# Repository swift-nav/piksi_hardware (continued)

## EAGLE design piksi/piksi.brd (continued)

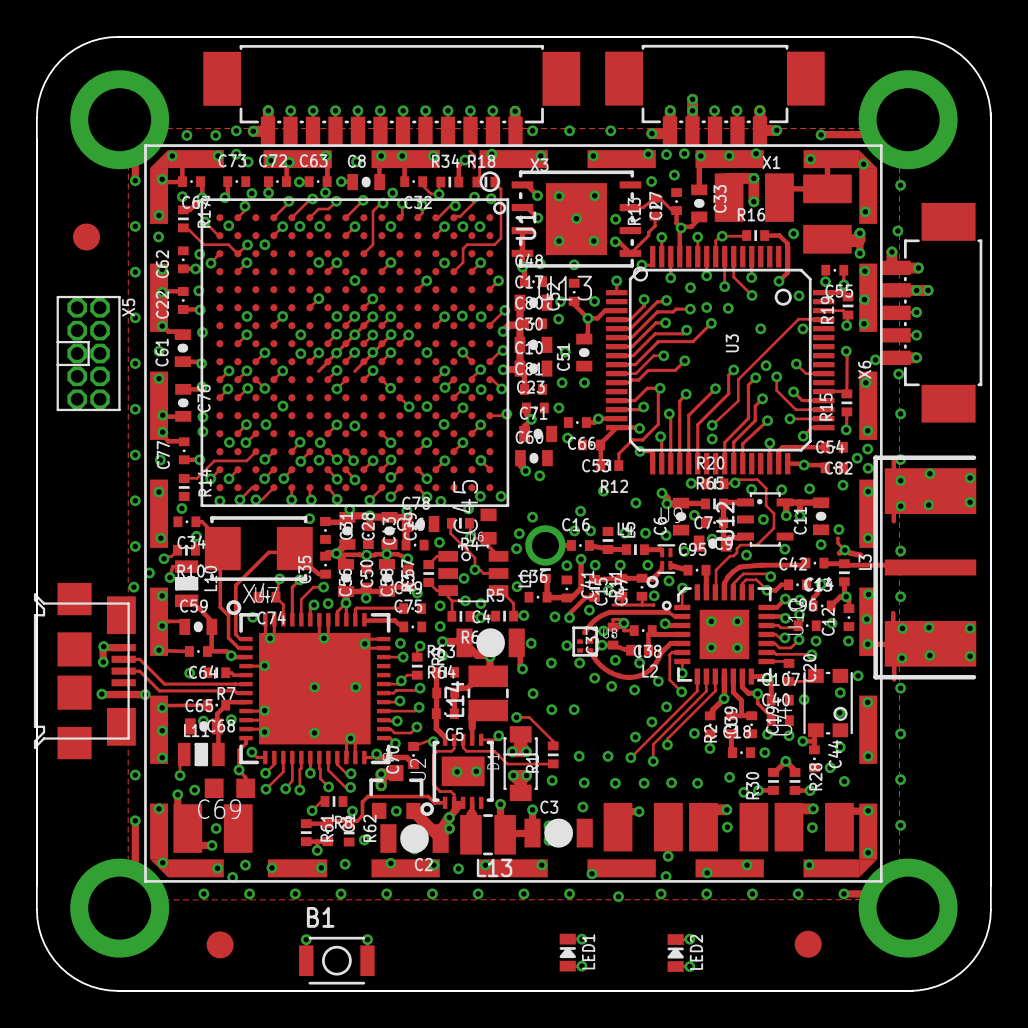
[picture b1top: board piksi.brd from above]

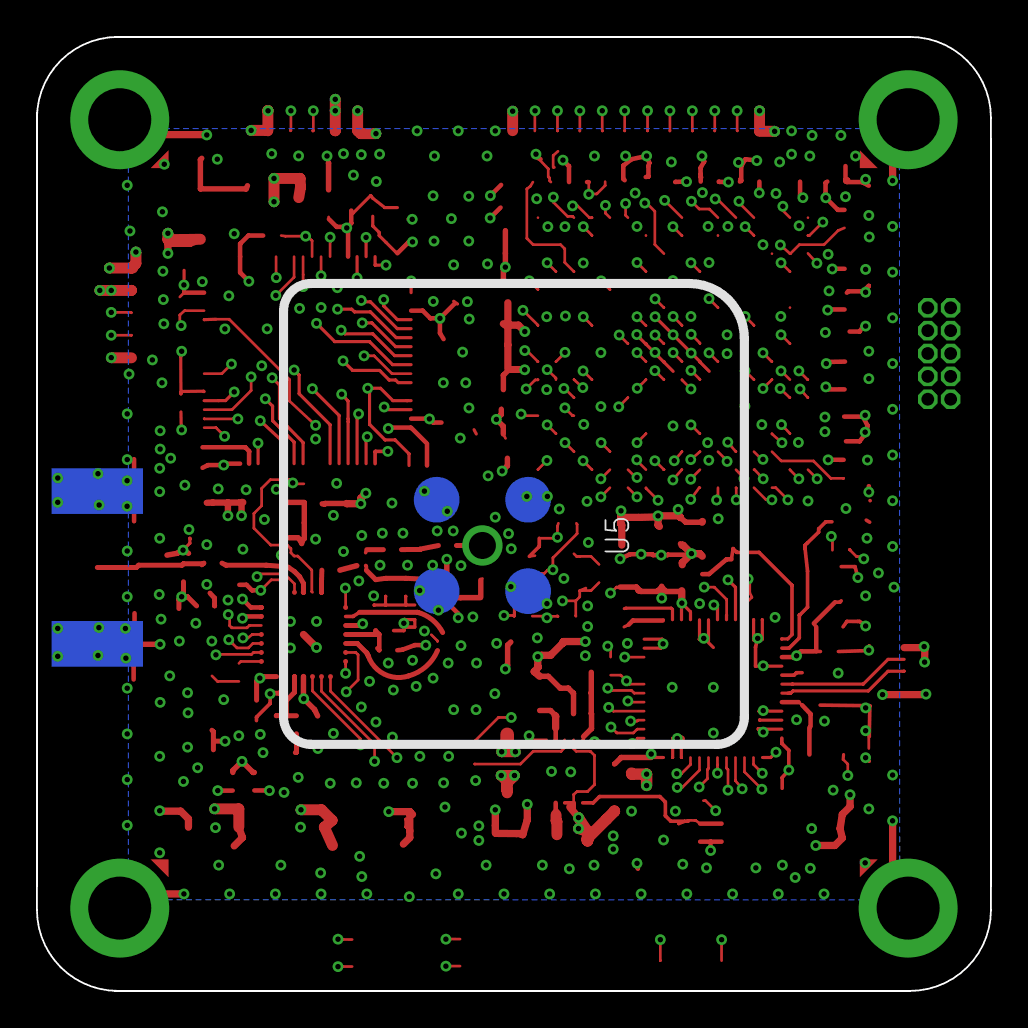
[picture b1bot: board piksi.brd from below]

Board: 6 copper layers, 53.0 x 53.0 mm, 157 parts (2 on the bottom side), 115 nets.

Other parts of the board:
U$1: LOGOINITIALS; INITIALS

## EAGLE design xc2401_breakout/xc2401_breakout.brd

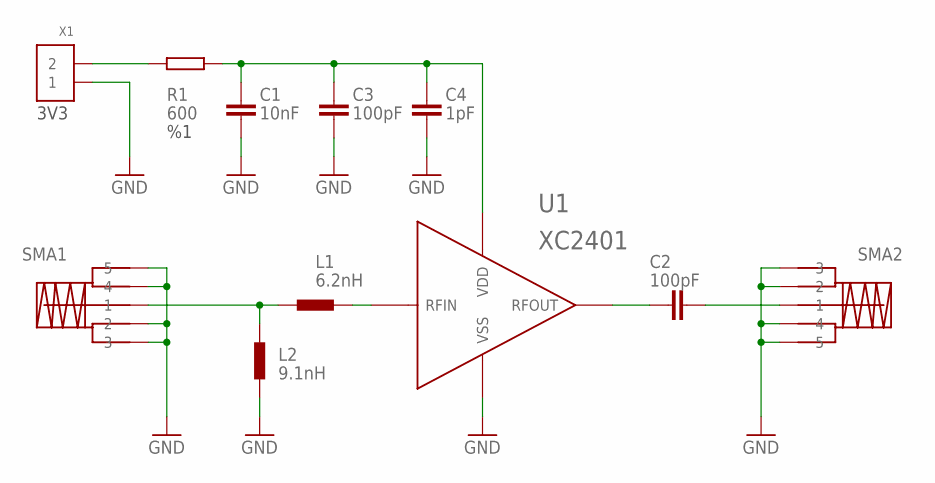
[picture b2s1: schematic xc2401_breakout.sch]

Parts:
C1: 10nF; 0402-CAP
C2, C3: 100pF; 0402-CAP
C4: 1pF; 0402-CAP
L1: 6.2nH; 0402-IND
L2: 9.1nH; 0402-IND
R1: 600; 0402-RES
SMA1, SMA2: SMA_EDGE
U1: XC2401
X1: CONN_2-1-53261; PB-53261-02

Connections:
GND: C1.P$2 (2), C3.P$2 (2), C4.P$2 (2), L2.P$1 (1), SMA1.P2 (2), SMA1.P3 (3), SMA1.P4 (4), SMA1.P5 (5), SMA2.P2 (2), SMA2.P3 (3), SMA2.P4 (4), SMA2.P5 (5), U1.3 (VSS), X1.1
unnamed: C1.P$1 (1), C3.P$1 (1), C4.P$1 (1), R1.P$2 (2), U1.1 (VDD)
unnamed: C2.P$1 (1), U1.2 (RFOUT)
unnamed: C2.P$2 (2), SMA2.P1 (1)
unnamed: L1.P$1 (1), L2.P$2 (2), SMA1.P1 (1)
unnamed: L1.P$2 (2), U1.4 (RFIN)
unnamed: R1.P$1 (1), X1.2

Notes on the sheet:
3V3

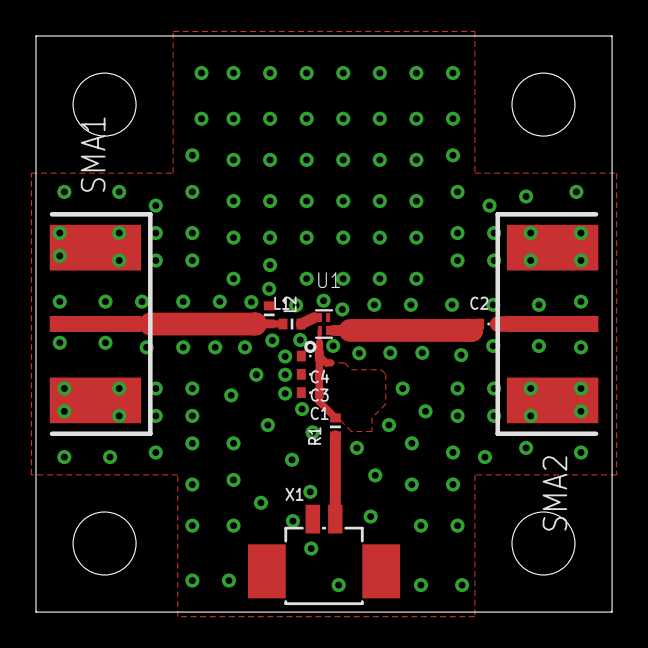
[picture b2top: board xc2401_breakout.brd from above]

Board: 2 copper layers, 32.0 x 32.0 mm, 11 parts (0 on the bottom side), 7 nets.

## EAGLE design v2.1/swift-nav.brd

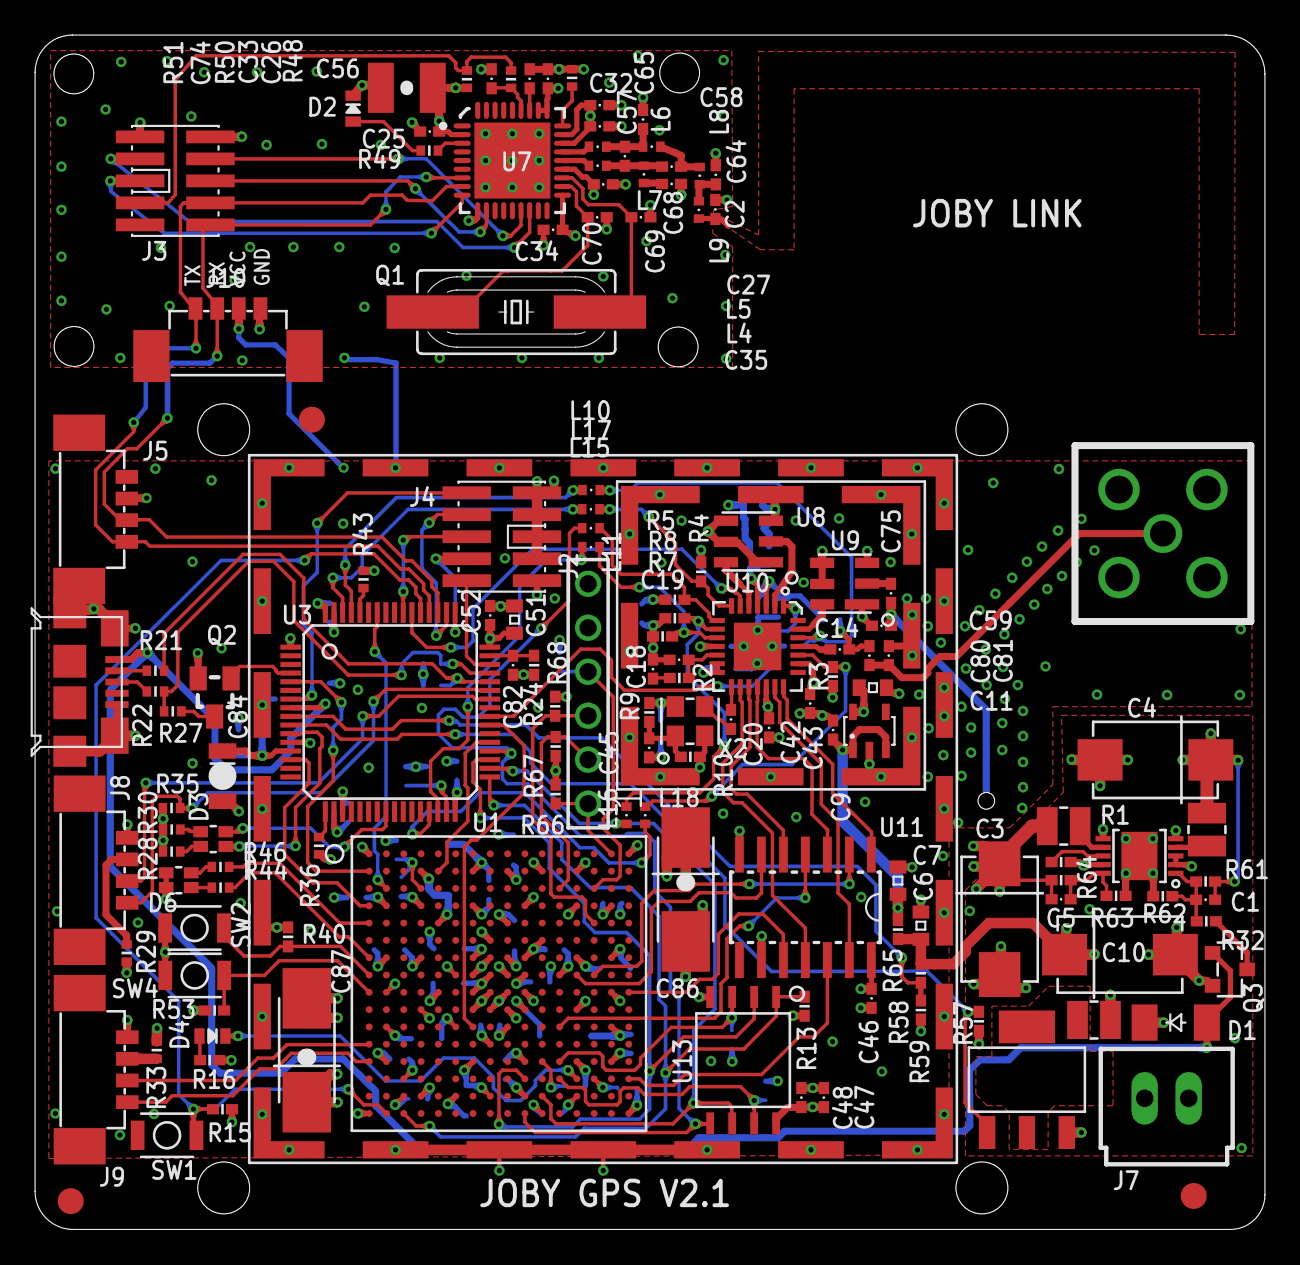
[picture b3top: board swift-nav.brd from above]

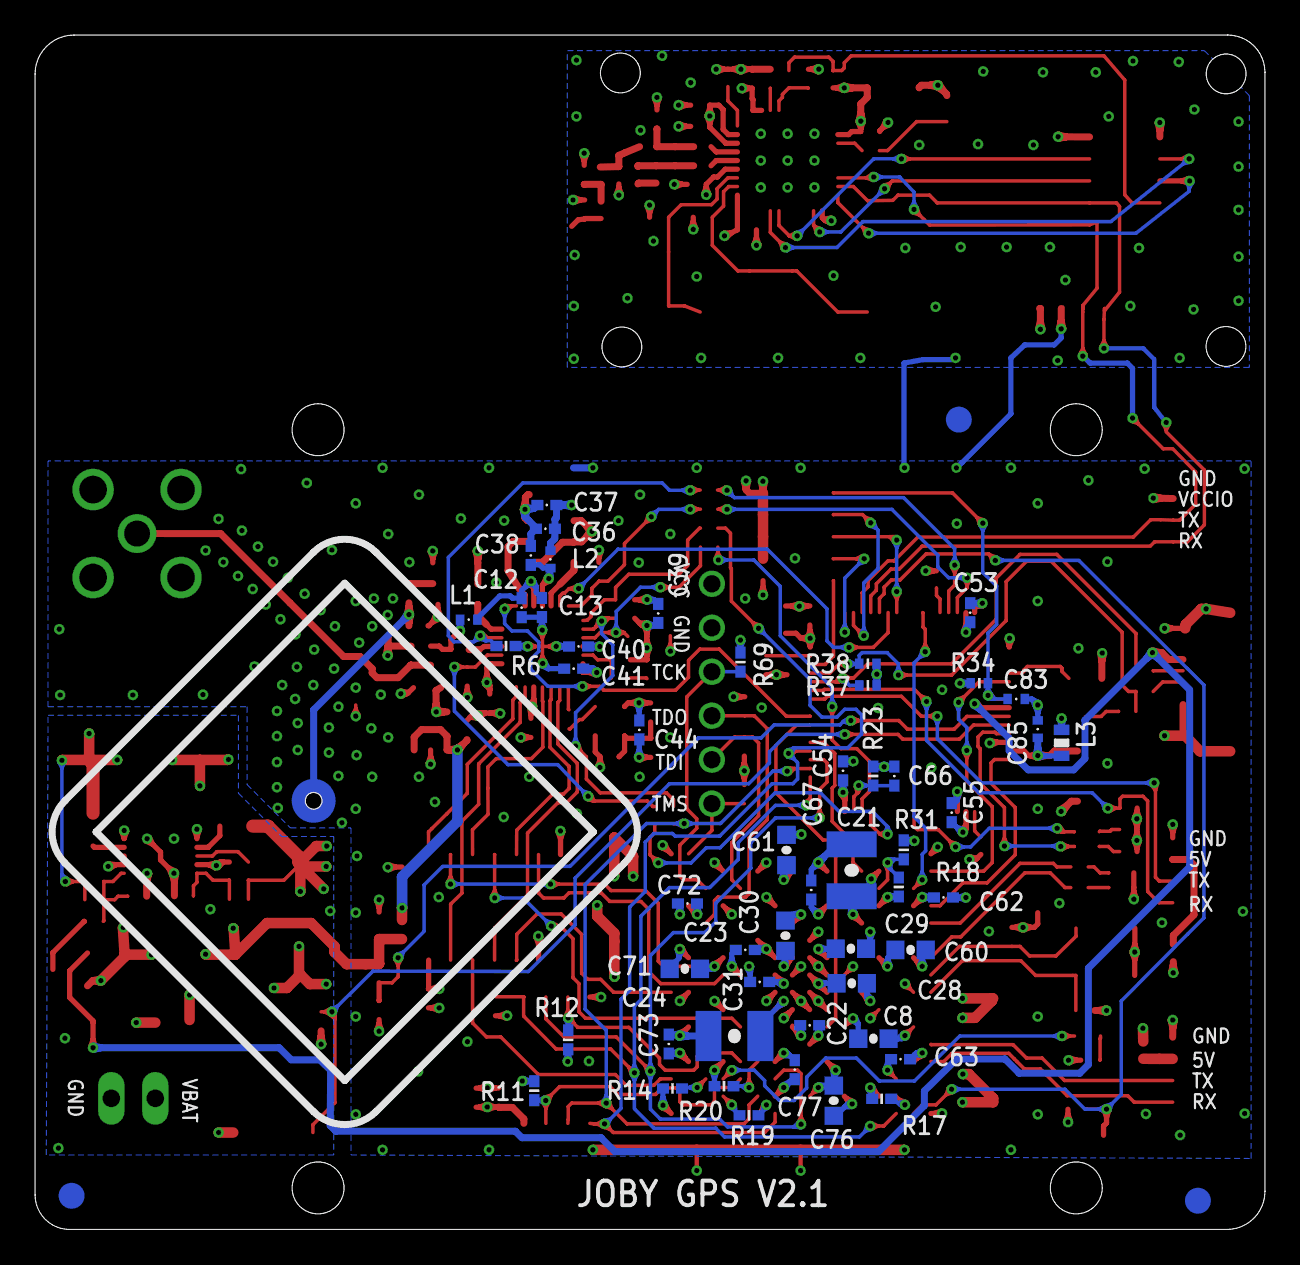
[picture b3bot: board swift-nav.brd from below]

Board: 4 copper layers, 71.0 x 69.0 mm, 198 parts (55 on the bottom side), 131 nets.

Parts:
ANT1: GPS_PATCH_ANTENNA
C1, C5: 22pF; C0402
C2, C59, C64, C81: DNP; C0402
C3, C4, C10: 10UF_TANT; CT7343
C6, C7: 2.2uF; 0603
C8, C28, C29, C30, C60, C61, C71, C76: 4.7uF; C0603K
C9, C44, C45, C48: 0.01uF; C0402
C11: 10uF; 0603
C12, C14, C37, C68: 100pF; C0402
C13, C20, C25, C26, C27, C32, C34, C35, C36, C39, C40, C41, C42, C43, C46, C52, C53, C54, C55, C66, C82: 0.1uF; C0402
C18: 0.47nF; C0402
C19: 27pF; C0402
C21, C24, C56: 100uF; C1210K
C22, C23, C31, C62, C63, C67, C72, C73, C77: 0.47uF; C0402
C33, C47, C58: 1uF; C0402
C38: 12pF; C0402
C51: 4.7uF; 0603
C57: 1pF; C0402
C65: 1.5pF; C0402
C69, C70: 33pF; C0402
C74: 1000pF; C0402
C75, C80: 0R; C0402
C83: 100nF; 0402-CAP
C84: 1uF; 1206-POL-CAP
C85: 10nF; 0402-CAP
C86, C87: 220uF; 6032/C
D1: 1N581; SOD-123_MINI-SMA
D2, D4: LED-0603; 0603-LED
D3, D6: LTST-C195KGJRKT
DRILEGEND: DRILEGEND
J1: SMA
J2: 6_PIN_100MIL; SSW-106-02-S-S
J3: DEBUG HDR; FTSH-105-DV
J4: PIN_HDR_EDG_1.27MM_5-2; FTSH-105-DV
J5, J10: RF LINK; PB-53398-04
J6: ZX62-B-5PA
J7: C-GRID-02-70543; 70543-02
J8: CON_UART1; PB-53398-04
J9: CON_UART3; PB-53398-04
JP5, JP6, JP7, JP8, JP9, JP10: FIDUCIAL1.5X3; FIDUCIAL-1.5X3
L1: 250nH/DNP; 0402-IND
L2: 36nH; 0402-IND
L3: 0603-IND@1
L4, L5: 12nH; 0402-IND
L6, L7: 18nH; 0402-IND
L8, L9: DNP; 0402-IND
L10, L11, L15, L16, L17, L18: 0402-IND
L12, L13, L14: 4.7uH; LQM2HPN4R7MG0L
Q1: 26MHz; HC49UP
Q2: DDTA143; SOT23
Q3: 2N7002
Q5: FDT458P; FDT458P_SOT223
R1: 100K; R0402
R2: 20k; R0402
R3, R4, R5, R6, R7, R8, R14, R66, R67, R68, R69: 10K; R0402
R9, R10, R58, R59: 10k; R0402
R11, R12: 100k; R0402
R13, R15, R17, R18, R19, R20, R40, R53, R57: 4K7; R0402
R16: 300; R0402
R21, R22: 22R; 0402-RES
R23, R24: 0ohm/DNP; R0402
R27: 1K5; 0402-RES
R28, R30, R44, R46: 150; 0402-RES
R29, R33: 0/DNP; 0402-RES
R31: 0R/DNP; R0402
R32: 475K; R0402
R34, R51: 10k; 0402-RES
R35, R36, R37, R38, R43, R50: 2k7; 0402-RES
R48: 56k; 0402-RES
R49: 270; 0402-RES
R61: 634K; R0402
R62: 200K; R0402
R63, R64: 200k; R0402
R65: 10; R0402
SHLD1: BMI-S-202
SHLD2: BMI-S-208
SW1, SW2, SW4: B3U-1000P
U1: 6SLX9FTG256; FT256
U2: LTC3407A; MSOP10
U3: STM32-M-64-LQFP; LQFP64
U7: CC1110; QFN50P595X595X90-37N
U8, U9: B4050
U10: MAX2769
U11: SN74LVC07A_SOIC
U12: PT7M8206B33TA5EX
U13: M25PX80; M25P
X2: ASVTX-11

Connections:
5VUSB: D1.A, J6.PIN_1, Q3.G, U3.8
16MHZ_FPGA_OUT: U1.B1, U3.5
+5V: D1.C, Q5.3, R29.P$1, R33.P$1
BATT_CHARGE_GATE: Q5.1, R57.1, U3.10
BOOT0: R43.P$2, U3.60
CS: L11.P$1, R7.2, U10.10
FE_CLK: C20.2, X2.4
FPGA_BUTT0: R53.2, SW4.P$2, U1.J1
FPGA_BUTT1: R40.2, SW2.P$2, U1.H1
FPGA_CONF: R15.2, SW1.P$2, U1.T2, U3.53
FPGA_D1_MISO2: R12.1, U1.N12, U13.P$3
FPGA_D2_MISO3: R11.1, U1.P12, U13.P$7
FPGA_LED0: R46.P$2, U1.E1
FPGA_LED1: R44.P$2, U1.G1
FPGA_M0: R19.1, U1.T11
FPGA_M1: R20.2, U1.N11
FPGA_TCK: J2.4, R69.2, U1.C14
FPGA_TDI: J2.2, R67.2, U1.C12
FPGA_TDO: J2.3, R68.2, U1.E14
FPGA_TMS: J2.1, R66.2, U1.A15
FT_USB_DM: J6.PIN_2, R21.P$1
FT_USB_DP: J6.PIN_3, R22.P$1
GND: C2.2, C3.-, C4.-, C6.1, C7.1, C8.2, C9.2, C10.-, C11.1, C12.2, C13.2, C18.2, C19.2, C21.2, C22.2, C23.2, C24.2, C25.2, C26.2, C27.2, C28.2, C29.2, C30.2, C31.2, C32.2, C33.2, C34.2, C35.2, C36.2, C37.2, C38.2, C39.2, C40.2, C41.2, C42.2, C43.2, C44.2, C45.2, C46.2, C47.2, C48.2, C51.1, C52.2, C53.2, C54.2, C55.2, C56.2, C59.1, C60.2, C61.2, C62.2, C63.2, C64.2, C65.2, C66.2, C67.2, C68.2, C69.2, C70.2, C71.2, C72.2, C73.2, C74.2, C76.2, C77.2, C81.1, C82.1, C83.P$1, C84.-, C85.P$1, C86.-, C87.-, D2.C, D6.GC, D6.RC, J1.P$2, J1.P$3, J1.P$4, J1.P$5, J2.5, J3.1, J4.3, J4.5, J4.7, J4.9, J5.1, J6.GND_LEFT, J6.GND_RIGHT, J6.GND_UP_LEFT, J6.GND_UP_RIGHT, J6.PIN_5, J7.2, J8.1, J9.1, J10.4, Q3.S, R6.1, R7.1, R8.1, R10.1, R14.2, R18.1, R20.1, R23.2, R24.1, R40.1, R43.P$1, R48.P$2, R53.1, R59.1, R62.2, R63.2, SHLD1.1, SHLD1.2, SHLD1.3, SHLD1.4, SHLD1.5, SHLD1.6, SHLD1.7, SHLD1.8, SHLD1.9, SHLD1.10, SHLD1.11, SHLD1.12, SHLD2.1, SHLD2.2, SHLD2.3, SHLD2.4, SHLD2.5, SHLD2.6, SHLD2.7, SHLD2.8, SHLD2.9, SHLD2.10, SHLD2.11, SHLD2.12, SHLD2.13, SHLD2.14, SHLD2.15, SHLD2.16, SHLD2.17, SHLD2.18, SHLD2.19, SHLD2.20, SHLD2.21, SHLD2.22, SHLD2.23, SHLD2.24, SHLD2.25, SHLD2.26, SHLD2.27, SHLD2.28, SW1.P$1, U1.A1, U1.A16, U1.B7, U1.B11, U1.D4, U1.D13, U1.E9, U1.G2, U1.G8, U1.G15, U1.H7, U1.H9, U1.H12, U1.J5, U1.J8, U1.K7, U1.K9, U1.L2, U1.L15, U1.M8, U1.N13, U1.P3, U1.R6, U1.R10, U1.T1, U1.T16, U2.5, U2.GP, U3.12, U3.18, U3.63, U7.37, U8.1, U8.3, U8.4, U8.5, U9.1, U9.3, U9.4, U9.5, U10.29, U11.7, U11.9, U12.2, U13.P$4, X2.3
JTAG_RST: C83.P$2, J4.10, R34.P$1, U3.7
JTAG_TCK: J4.4, U3.49
JTAG_TDI: J4.8, U3.50
JTAG_TDO: J4.6, U3.55
JTAG_TMS: J4.2, U3.46
LINK_RX: J3.8, J5.4, J10.1, U3.52, U7.8
LINK_TX: J3.10, J5.3, J10.2, U3.51, U7.7
MAX_ANT_FLAG: U3.40, U10.1
MAX_CLKOUT: U1.J16, U11.10
MAX_I0: U1.P16, U11.12
MAX_I1: U1.H14, U11.2
MAX_LD: U3.54, U10.6
MAX_NCS: L11.P$2, U3.30
MAX_NIDLE: L18.P$2, U3.29
MAX_NSHDN: L17.P$2, U3.62
MAX_PGM: L10.P$2, U3.61
MAX_Q0: U1.L12, U11.4
MAX_Q1: U1.H13, U11.6
unnamed: Q2.3, R27.P$2
unnamed: J8.2, R29.P$2
unnamed: C18.1, R2.1
unnamed: C19.1, R2.2, U10.12
unnamed: U8.2, U10.2
unnamed: C20.1, U10.15
unnamed: U8.6, U10.5
unnamed: C80.2, C81.2, J1.P$1
unnamed: U10.18, U11.3
unnamed: C12.1, C13.1, L1.P$2, U10.3
unnamed: C75.1, U9.2
unnamed: Q3.D, R32.2
unnamed: D4.C, U1.P13
unnamed: R1.1, U2.8
unnamed: L13.2, U2.4
unnamed: J9.2, R33.P$2
unnamed: D6.RA, R46.P$1
unnamed: U10.16, U11.11
unnamed: U10.17, U11.5
unnamed: C38.1, L2.P$1, U10.4
unnamed: D6.GA, R44.P$1
unnamed: D3.GA, R30.P$1
unnamed: L12.2, Q5.2, Q5.4
unnamed: L14.1, U2.7
unnamed: C45.1, R9.1, R10.2, X2.1
unnamed: U10.21, U11.1
unnamed: U9.6, U10.27
unnamed: C14.2, U10.25
unnamed: R18.2, R31.2, U1.C4
unnamed: U10.20, U11.13
unnamed: C57.2, C65.1, L5.P$2, L6.P$1
unnamed: R14.1, U1.P14
unnamed: C33.1, U7.30
unnamed: C57.1, C58.1, L4.P$2, L7.P$1
unnamed: L4.P$1, U7.23
unnamed: L5.P$1, U7.24
unnamed: D3.GC, U3.24
unnamed: C69.1, Q1.1, U7.21
unnamed: D4.A, R16.1
unnamed: R17.2, U1.R3
unnamed: C58.2, L6.P$2, L8.P$2
unnamed: C64.1, L8.P$1, L9.P$2
unnamed: ANT1.P$1, C59.2, C75.2
unnamed: C14.1, C80.1, L1.P$1
unnamed: C68.1, L7.P$2
unnamed: C70.1, Q1.2, U7.20
unnamed: R48.P$1, U7.27
unnamed: D2.A, R49.P$1
unnamed: C2.1, L9.P$1
unnamed: C74.1, R50.P$2, U7.31
unnamed: C1.1, R32.1, R61.1, R62.1, U2.1
unnamed: C5.2, R63.1, R64.1, U2.10
unnamed: D3.RA, R28.P$2
unnamed: C7.2, C9.1, R65.2, U12.1, U12.3
unnamed: D3.RC, U3.11
NIDLE: L18.P$1, R3.1, U10.24
NSHDN: L17.P$1, R4.1, U10.7
P0_4-SSN: J3.5, U7.9
P0_5-SCK: J3.6, U7.11
P1_1-LED: R49.P$2, U7.3
P2_1-DD: J3.4, U7.15
P2_2-DC: J3.3, U7.16
PGM: L10.P$1, R6.2, U10.26
RESET_N: J3.7, R50.P$1, R51.P$1
SCLK: L16.P$1, R8.2, U10.9
SDATA: L15.P$1, R5.1, U10.8
SPI_CS: R13.1, U1.T3, U3.33, U13.P$1
SPI_FPGA_CS: U1.L7, U3.39
SPI_MISO: U1.P10, U3.35, U13.P$2
SPI_MOSI: L15.P$2, U1.T10, U3.36, U13.P$5
SPI_SCK: L16.P$2, U1.R11, U3.34, U13.P$6
TIM2CH1: U1.D1, U3.14
TIM3CH1: U1.B5, U3.37
TIM4CH1: U1.C2, U3.58
UART1_RX: J8.4, R35.P$2, U3.43
UART1_TX: J8.3, U3.42
UART2_RX: R36.P$2, U3.17
UART3_RX: J9.4, U1.N1
UART3_TX: J9.3, U1.M1
USB_DISC: Q2.1, U3.4
USB_DM: R21.P$2, R37.P$2, U3.44
USB_DP: R22.P$2, R27.P$1, R38.P$2, U3.45
V+: C6.2, C10.+, J7.1, L12.1, R1.2, R57.2, R58.2, R65.1, U2.2, U2.3, U2.6, U2.9
VBAT_MONITOR: R58.1, R59.2, U3.9
VCC: C11.2, C36.1, C37.1, C39.1, C40.1, C41.1, C42.1, C43.1, C44.1, L2.P$2, R3.2, R4.2, R5.2, R9.2, U10.11, U10.13, U10.14, U10.19, U10.23, U12.5, X2.6
VCCINT: C3.+, C5.1, C24.1, C28.1, C29.1, C30.1, C31.1, L14.2, R64.2, U1.G7, U1.G9, U1.H8, U1.H10, U1.J7, U1.J9, U1.K8, U1.K10
VCCIO: C1.2, C4.+, C8.1, C21.1, C22.1, C23.1, C25.1, C26.1, C27.1, C32.1, C34.1, C35.1, C46.1, C47.1, C48.1, C51.2, C52.1, C53.1, C54.1, C55.1, C56.1, C60.1, C61.1, C62.1, C63.1, C67.1, C71.1, C72.1, C73.1, C76.1, C77.1, C86.+, C87.+, J2.6, J3.2, J4.1, J5.2, J10.3, L3.P$1, L13.1, Q2.2, R11.2, R12.2, R13.2, R15.1, R16.2, R17.1, R19.2, R28.P$1, R30.P$2, R31.1, R34.P$2, R35.P$1, R36.P$1, R37.P$1, R38.P$1, R51.P$2, R61.2, R66.1, R67.1, R68.1, R69.1, SW2.P$1, SW4.P$1, U1.B4, U1.B9, U1.B13, U1.D2, U1.D7, U1.D10, U1.D15, U1.E5, U1.F8, U1.F11, U1.G4, U1.G10, U1.G13, U1.H6, U1.J2, U1.J10, U1.J15, U1.K4, U1.K13, U1.L6, U1.L9, U1.N2, U1.N7, U1.N10, U1.N15, U1.R4, U1.R8, U1.R13, U3.1, U3.19, U3.32, U3.48, U3.64, U7.2, U7.10, U7.19, U7.22, U7.25, U7.26, U7.28, U7.29, U11.14, U13.P$8
VDDA: C84.+, C85.P$2, L3.P$2, U3.13
VSS1: C66.1, R23.1, U3.31
VSS2: C82.2, R24.2, U3.47

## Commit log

2012-03-06 Initial import of JobyGNSS v2.1 design in Eagle 5 format.
2012-03-06 Renamed and converted to Eagle 6 format.
2012-03-10 Need to add different TCXO to schematic then ready for review
2012-03-12 Changed TXCO to TXC 7Q-16.368MBG-T (3v3, 16.368MHz, 0.5/2 2PPM TCXO) And added library with 7Q-16.368MBG-T package in it
2012-03-12 Rearranged schematic a bit and cleared up some errors
2012-03-14 Some changes post schematic review, more to come... Removed FPGA_D1_MISO2 and FPGA_D2_MISO3, changed R12 and R11 to hard shorts to VCCIO Removed Molex connector Replaced all +5V power symbols with V+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
2012-03-14 Removed ferrite leading to VDDA pin on STM Changed UART headers to 5 pin with both 3v3 and V+ pins Changed STM32-LQFP64 symbol to F4 (VCAP_1 and VCAP_2 replace VSS1 and VSS2)
2012-03-14 Added button to JTAG_RST line Added libraries used in design of 2.1
2012-03-15 Starting layout
2012-03-16 Working on the layout
2012-03-20 Workin on layout. Finished placing everything but a few resistors. Should we size down to a smaller can? Add FTDI 232H?
2012-03-20 RF section routed
2012-03-21 Starting placing FT232H components
2012-03-22 Hooking up FTDI to FPGA
2012-03-23 All components placed, but clearances aren't going to be enough for assembly so have to move stuff to the bottom side.
2012-03-23 All components placed inside can with 20 mil clearances for assembly
2012-03-27 Just a bit of routing between the STM and FPGA left
2012-03-27 Finished routing
2012-03-28 Forgot to route debug header nets
2012-03-28 Schematic warnings checked, no problems
2012-03-28 Fixing DRC errors on board
2012-03-28 DRC complete
2012-03-29 Corrected ground plane / traces under side mount SMA and straightened some traces
2012-03-30 Cleaned up routing somewhat, shortened trace lengths where easy to do so
2012-03-30 Changed positions of picoblade headers and JTAG header, re-routing Rotated Spartan6 180 degrees
2012-03-31 Routing rearranged board, changed position of FT232
2012-04-03 All signals routed except caps on bottom layer
2012-04-03 Caps placed on bottom and board cleaned up a bit
2012-04-03 Some clean-up and DRC done. Errors left un-approved in DRC are cases where via-to-pad spacing or pad-to-pad spacing (same signal) is less than 6 mil
2012-04-03 Few more minor changes, cleaned up top silkscreen a bit
2012-04-04 Cleaned up soldermask clearances
2012-04-04 Removed last airwire (not that it was a problem).
2012-04-04 Starting work on silkscreen.
2012-04-04 Moved LEDs out a bit for silkscreen.
2012-04-04 More silkscreen fiddling
2012-04-04 Bottom silk should be mirrored (duh). Added initial attempt at logo.
2012-04-04 Changed mounting holes to fit an M3 bolt and to be plated through.
2012-04-04 Adding dimensions to Document layer.
2012-04-04 More silk changes.
2012-04-04 Trying a new logo font.
2012-04-04 Fix small error in logo.
2012-04-04 Moved around a few vias and added a few more.
2012-04-04 Stuffed in a bunch more vias
2012-04-04 Yet more vias.
2012-04-04 Fix restrict layer on fiducials.
2012-04-04 Move fiducial
2012-04-04 Move a different fiducial.
2012-04-04 Changing cream
2012-04-04 VUSB pulldown + other shiz
2012-04-04 UART6 solder jumper for bus contention.
2012-04-05 Looots of stuff
2012-04-05 More stuff
2012-04-05 Changed FT232 AC7 pullup to V_USB instead of VCCIO Changed RF input from V+ (before PMOS) to VDD (after PMOS) Added pulldown resistor to V_USB
2012-04-05 Removed extra mounting hole. Still need to move mounting holes in
2012-04-05 Changed hole separation to 43.8mm
2012-04-05 Cut off corners of BMIS-208 shield to accomodate mounting holes. Need to shrink mounting hole pads
2012-04-05 Changed mounting hole copper width to 5.5 mm to give clearance to shield. Now 7 mil soldermask clearance between mounting hole and shield
2012-04-05 Removed C47 and changed C48 from 0.01uF to 0.1uF
2012-04-06 Some small changes to silk, schem annotations.
2012-04-06 About to tape out
2012-04-06 Version 2.2 Gerbers as sent for production.
2012-04-06 Adding mechanical outline gerber file
2012-04-06 Removing v2.2 production gerber files.
2012-04-09 Consolidated some more part values
2012-05-18 Added XC2401 GPS LNA breakout board and put v2.2 in its own folder
2012-05-18 Renamed lna_breakout to xc2401 breakout
2012-05-18 Putting v2.1 files in their own folder (just same files as v2_1 tag)
2012-05-18 Changed board dims to 1.25x1.25 in for barebones specs Added more bare area around holes
2012-05-18 Forgot to lengthen transmission lines
2012-05-18 Added frame to schematic
2012-05-24 Initial add of v2.3 files
2012-05-24 Added extra pages and partitioned design amongst pages to make it more neat. Snapped components and connections to grid where they weren't 100 mil snapped.
2012-05-24 In schematic: -Resistor between V_USB and STM USB detect pin -Add more FIFO lines from FPGA -Removed internal shield -Added LNA and associated components to LNA1 line -Changed LNA1 SMA to 1 thru hole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
2012-05-25 Cleaned up RF section a little bit. Going to split MAX2769 symbol up a little bit more to clean it up further.
2012-05-25 Cleaned up RF section a bit more - separated max2769 into 3 symbols
2012-05-25 Added pull up resistors to NIDLE and NSHDN and pull down to PGM
2012-05-25 Changed debug header to 12 pin with 1 gnd 1 VDD and 10 signal connections
2012-05-25 Removed capacitors from bottom of board
2012-05-25 Removed fiducials from bottom of board
2012-05-25 Debug connector was connected to VDD instead of V+ (post instead of pre-reverse polarity protection)
2012-05-26 Changed cap footprints to smaller versions
2012-05-26 Moved LNA2 SMA to line up with shield opening better
2012-05-30 Routed some FTDI signals
2012-05-30 Routed rest of FTDI signals and added resistor to V_USB
2012-05-30 Finished placing all components on board
2012-05-30 Workin it
2012-05-31 Couple more signals to re-route
2012-05-31 Gettin 'er done
2012-06-01 Gettin' urr dunn
2012-06-06 Moving around some vias to reduce large gaps in ground plane
2012-06-07 Finished moving stuff around, routing, and DRC. Need to look at soldermask.
2012-06-07 Couple part moves for spacing / solder mask clearance
2012-06-07 python script to extract consolidated bom (by same part) from .bom file generated by the bom ulp
2012-06-08 Silkscreen and logo updated for v2.3
2012-06-09 v2.3 as sent out for production
2012-06-11 Removing 2.3 gerbers
2012-06-11 Updated footprints and board with proper paste sizes
2012-06-11 Gerbers for Guillermo kapton stencil
2012-06-11 Removing v2.3 Guillermo kapton stencil gerbers
2012-06-11 Gerbers for stencil with apertures for shield
2012-06-11 Removing cream gerbers
2012-07-03 Fixed stupid patch antenna ground pin via bug. Changed LNA footprint to 5 pin version. Fixed traces next to active antenna pin not meeting 6 mil clearance.
2012-07-03 DRC checked and now passing
2012-07-03 Moved vias around to make silkscreen better, and re-DRC'd
2012-07-03 Disconnecting USB shield from ground.
2012-07-03 DRC checked and approved for v2.3.1
2012-07-03 v2.3.1 as sent out for production
2012-07-03 Removing v2.3.1 gerbers
2012-07-25 Changed paste layer to make stencil gaps smaller and reduce probability of shorts during assembly
2012-07-25 Changed LNA and SAW stencil openings
2012-07-25 Stencil for v2.3.1
2012-07-25 Removing v2.3.1 stencil gerber
2012-08-15 Changed some RF matching inductor values and the red LED resistor value
2013-06-17 Changed revisions numbers from 2.3 to 2.3.1
2013-06-17 Cleaned up text in schematic a bit
2013-06-17 Cleaned up consolidate_bom.py a bit
2013-06-17 Removed v2.1 and v2.2 files
2013-06-17 Moved v2.3 folder to piksi folder
2013-06-17 Added Creative Commons Attribution Share-Alike 3.0 license
2013-06-17 Added text to README about files, copyright, and license
2013-06-17 Renamed piksi/swift_nav.* to piksi/piksi.*
2013-06-17 Use python from user's environment in consolidate_bom.py
2013-06-18 Remove sys import
2013-06-18 Changed text in README
2013-06-18 Changed frame, description, and added copyright/license notice for sheet 7
2013-06-18 Changed frame, description, and added copyright/license notice for sheet 6
2013-06-18 Changed frame, description, and added copyright/license notice for sheet 5
2013-06-18 Changed L1 inductor value to DNP
2013-06-18 Changed frame, description, and added copyright/license notice for sheet 4
2013-06-18 Changed frame, description, and added copyright/license notice for sheet 3
2013-06-18 Changed frame, description, and added copyright/license notice for sheet 2
2013-06-18 Changed frame, description, and added copyright/license notice for sheet 1
2013-06-18 Moved stuff around on connectors sheet
2013-06-18 Couple minor mods to schematic
2013-06-18 Update README for repo name change.
2013-06-18 Changed some text that looked weird in the pdf
2013-06-18 Changed A4 frames to A3
2013-06-27 Moved wire node up from USB pull down resistor for better cosmetics
2013-11-21 Fixed errors eagle 6.5 was complaining about
2013-11-21 Snapped all elements on schematic to 0.1 inch grid
2016-06-21 Board with new logo and updated library
2016-06-21 v2.3.1 gerbers with updated silkscreen logo
2016-06-21 Remove gerbers
